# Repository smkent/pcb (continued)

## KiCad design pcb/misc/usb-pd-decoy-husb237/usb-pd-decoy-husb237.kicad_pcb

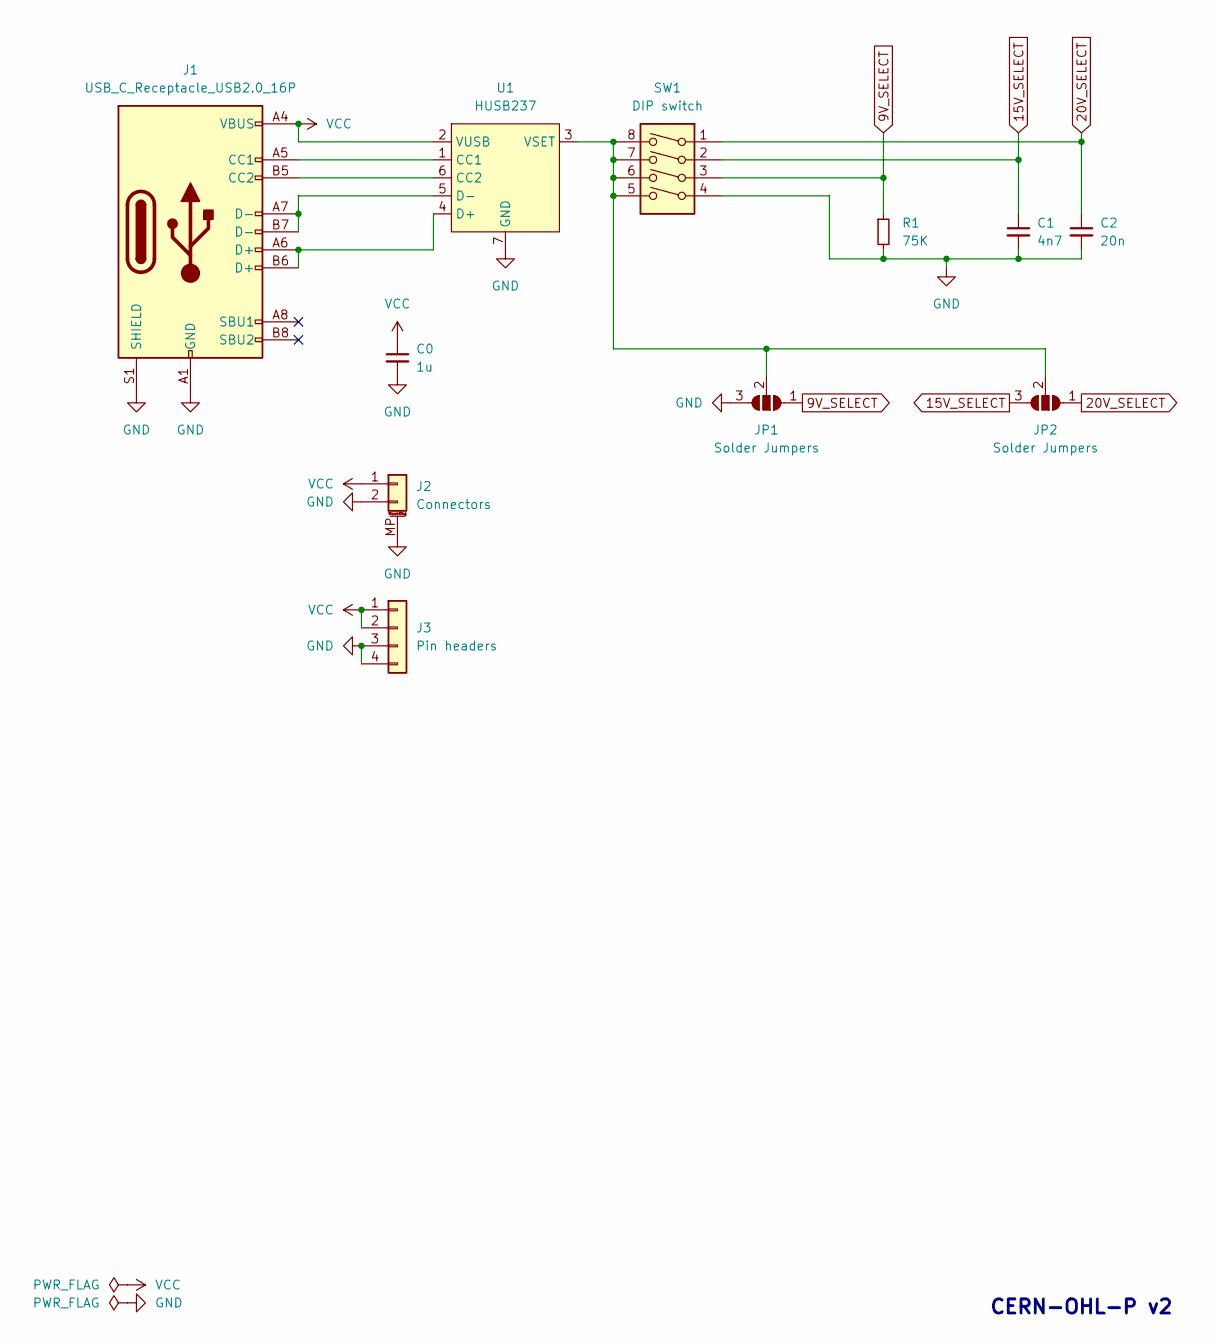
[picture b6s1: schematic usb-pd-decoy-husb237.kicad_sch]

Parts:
C0: 1u; C_0603_1608Metric_Pad1.08x0.95mm_HandSolder
C1: 4n7; C_0603_1608Metric_Pad1.08x0.95mm_HandSolder
C2: 20n; C_0603_1608Metric_Pad1.08x0.95mm_HandSolder
J1: USB_C_Receptacle_USB2.0_16P; USB_C_Receptacle_GCT_USB4105-xx-A_16P_TopMnt_Horizontal
J2: Connectors; Conn_Combo_TerminalBlock_JST-1x02-XH_PH-pad2gnd
J3: Pin headers; PinHeader_1x04_P2.54mm_Vertical_simple_pad3,4gnd
JP1, JP2: Solder Jumpers; SolderJumper-3_P1.0mm_Open_RoundedPad_simple
R1: 75K; R_0603_1608Metric_Pad0.98x0.95mm_HandSolder
SW1: DIP switch; SW_DIP_SPSTx04_Slide_P1.27mm
U1: HUSB237; DFN-6-1EP_2x2mm_P0.65mm_EP1x1.6mm; LCSC Part C7471904

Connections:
9V_SELECT: JP1.1 (A), R1.1, SW1.3
15V_SELECT: C1.1, JP2.3 (B), SW1.2
20V_SELECT: C2.1, JP2.1 (A), SW1.1
GND: C0.2, C1.2, C2.2, J1.A1 (GND), J1.A12 (GND), J1.B1 (GND), J1.B12 (GND), J1.S1 (SHIELD), J2.2, J2.MP (MountPin), J3.3, J3.4, JP1.3 (B), R1.2, SW1.4, U1.7 (GND)
unnamed: J1.A5 (CC1), U1.1 (CC1)
unnamed: J1.B5 (CC2), U1.6 (CC2)
unnamed: JP1.2 (C), JP2.2 (C), SW1.5, SW1.6, SW1.7, SW1.8, U1.3 (VSET)
unnamed: J1.A6 (D+), J1.B6 (D+), U1.4 (D+)
unnamed: J1.A7 (D-), J1.B7 (D-), U1.5 (D-)
VCC: C0.1, J1.A4 (VBUS), J1.A9 (VBUS), J1.B4 (VBUS), J1.B9 (VBUS), J2.1, J3.1, J3.2, U1.2 (VUSB)

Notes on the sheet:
CERN-OHL-P v2

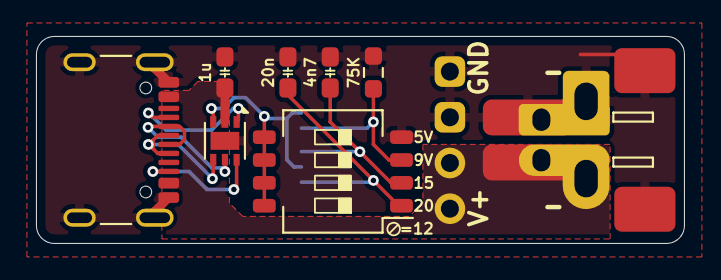
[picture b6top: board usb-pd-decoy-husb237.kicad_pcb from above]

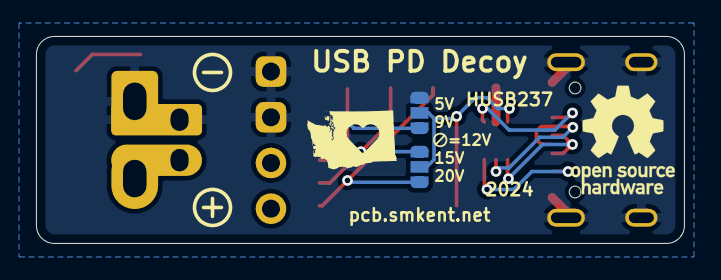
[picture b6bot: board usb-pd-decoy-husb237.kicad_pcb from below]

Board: 2 copper layers, 36.0 x 11.5 mm, 11 parts (3 on the bottom side), 10 nets.

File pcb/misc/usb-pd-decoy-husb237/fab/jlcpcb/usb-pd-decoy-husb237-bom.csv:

Comment,Designator,Footprint,LCSC
HUSB237,U1,Package_DFN_QFN:DFN-6-1EP_2x2mm_P0.65mm_EP1x1.6mm,C7471904
1u,C0,custom:C_0603_1608Metric_Pad1.08x0.95mm_HandSolder,
75K,R1,custom:R_0603_1608Metric_Pad0.98x0.95mm_HandSolder_simple,
20n,C2,custom:C_0603_1608Metric_Pad1.08x0.95mm_HandSolder,
DIP switch,SW1,custom:SW_DIP_SPSTx04_Slide_P1.27mm,
USB_C_Receptacle_USB2.0_16P,J1,connectors:USB-C-Receptacle-16P-TopMount-Horizontal,
4n7,C1,custom:C_0603_1608Metric_Pad1.08x0.95mm_HandSolder,
Pin headers,J3,"custom:PinHeader_1x04_P2.54mm_Vertical_simple_pad3,4gnd",
Connectors,J2,custom:Conn_Combo_TerminalBlock_JST-1x02-XH_PH-pad2gnd,

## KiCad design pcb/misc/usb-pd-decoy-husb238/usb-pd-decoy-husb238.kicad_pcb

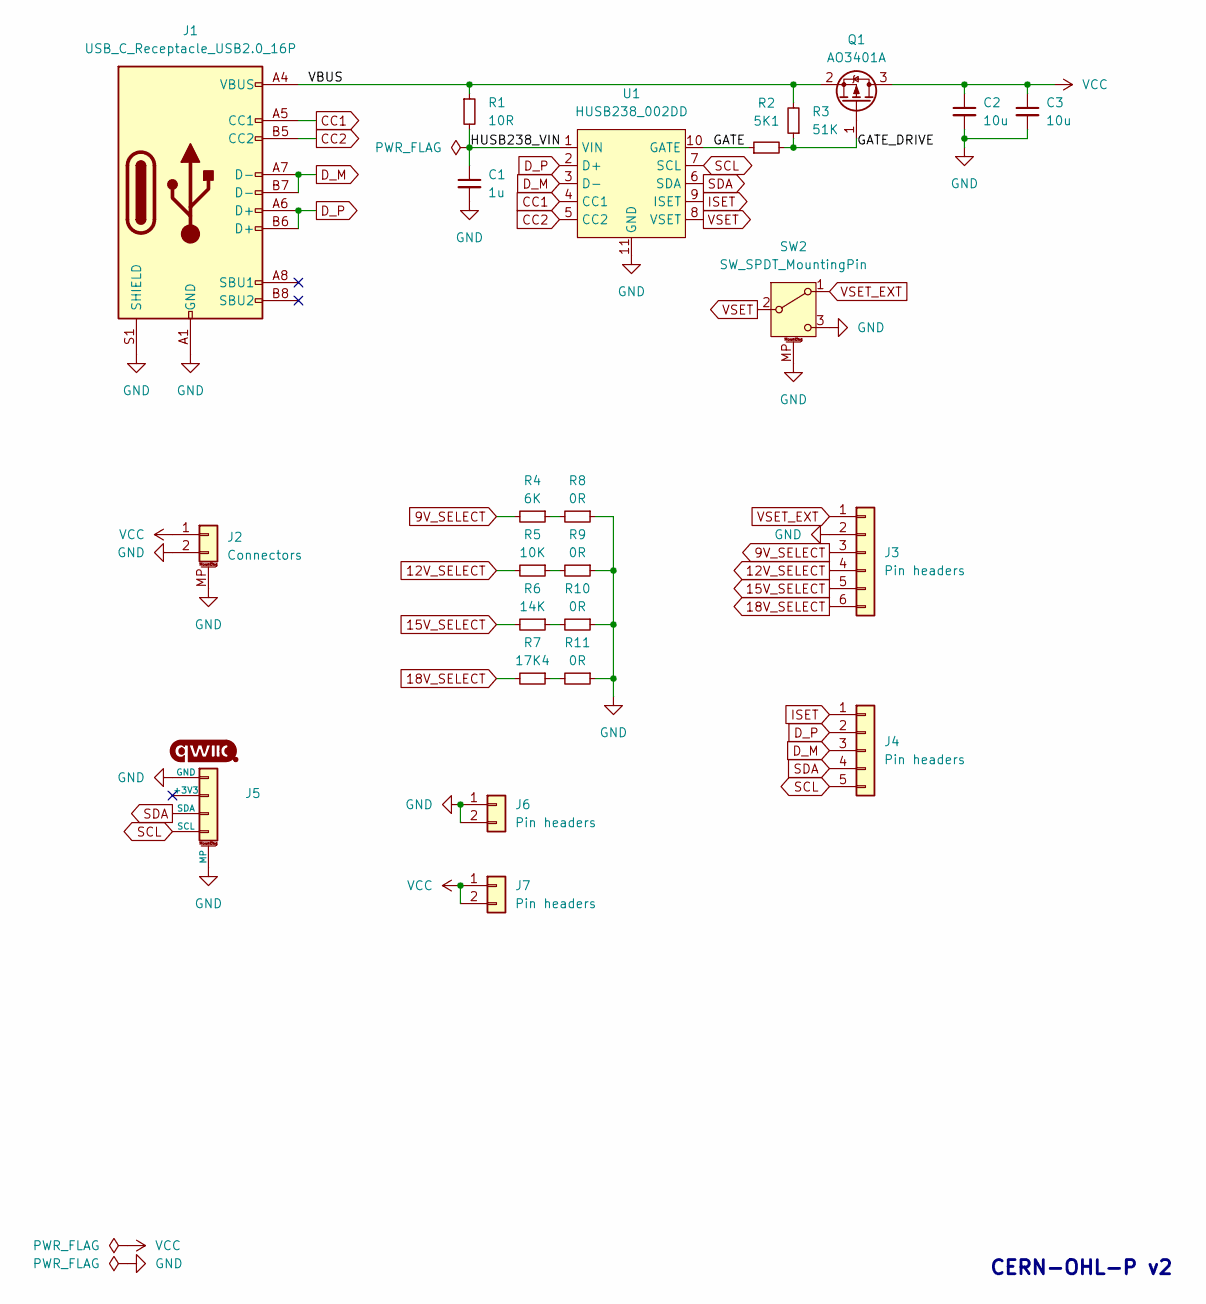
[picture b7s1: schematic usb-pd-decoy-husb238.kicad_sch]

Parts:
C1: 1u; C_0603_1608Metric
C2, C3: 10u; C_0603_1608Metric
J1: USB_C_Receptacle_USB2.0_16P; USB_C_Receptacle_GCT_USB4105-xx-A_16P_TopMnt_Horizontal
J2: Connectors; Conn_Combo_TerminalBlock_JST-1x02-XH_PH-pad2gnd
J3: Pin headers; PinHeader_1x06_P2.54mm_Vertical_simple
J4: Pin headers; PinHeader_1x05_P2.54mm_Vertical_simple
J5: Qwiic; Qwiic-SMD-horizontal-logo-bottom-pinout
J6, J7: Pin headers; PinHeader_1x02_P2.54mm_Vertical_simple
Q1: AO3401A; SOT-23
R1: 10R; R_0603_1608Metric
R2: 5K1; R_0603_1608Metric
R3: 51K; R_0603_1608Metric
R4: 6K; R_0603_1608Metric
R5: 10K; R_0603_1608Metric
R6: 14K; R_0603_1608Metric
R7: 17K4; R_0603_1608Metric
R8, R9, R10, R11: 0R; R_0603_1608Metric
SW2: SW_SPDT_MountingPin; SW_SPDT_PCM12
U1: HUSB238_002DD; WDFN-10-1EP_3x3mm_P0.5mm_EP1.8x2.5mm; LCSC Part C7471904

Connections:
9V_SELECT: J3.3, R4.2
12V_SELECT: J3.4, R5.2
15V_SELECT: J3.5, R6.2
18V_SELECT: J3.6, R7.2
/GATE: R2.1, U1.10 (GATE)
/GATE_DRIVE: Q1.1 (G), R2.2, R3.1
/HUSB238_VIN: C1.1, R1.2, U1.1 (VIN)
/VBUS: J1.A4 (VBUS), J1.A9 (VBUS), J1.B4 (VBUS), J1.B9 (VBUS), Q1.2 (S), R1.1, R3.2
CC1: J1.A5 (CC1), U1.4 (CC1)
CC2: J1.B5 (CC2), U1.5 (CC2)
D_M: J1.A7 (D-), J1.B7 (D-), J4.3, U1.3 (D-)
D_P: J1.A6 (D+), J1.B6 (D+), J4.2, U1.2 (D+)
GND: C1.2, C2.2, C3.2, J1.A1 (GND), J1.A12 (GND), J1.B1 (GND), J1.B12 (GND), J1.S1 (SHIELD), J2.2, J2.MP (MountPin), J3.2, J5.1 (GND), J5.MP, J6.1, J6.2, R8.1, R9.1, R10.1, R11.1, SW2.3 (C), SW2.MP (MountPin), U1.11 (GND)
ISET: J4.1, U1.9 (ISET)
unnamed: R4.1, R8.2
unnamed: R5.1, R9.2
unnamed: R6.1, R10.2
unnamed: R7.1, R11.2
SCL: J4.5, J5.4 (SCL), U1.7 (SCL)
SDA: J4.4, J5.3 (SDA), U1.6 (SDA)
VCC: C2.1, C3.1, J2.1, J7.1, J7.2, Q1.3 (D)
VSET: SW2.2 (B), U1.8 (VSET)
VSET_EXT: J3.1, SW2.1 (A)

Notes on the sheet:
CERN-OHL-P v2

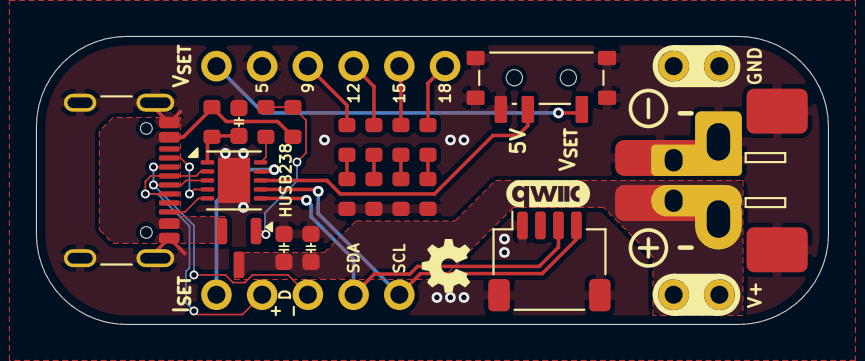
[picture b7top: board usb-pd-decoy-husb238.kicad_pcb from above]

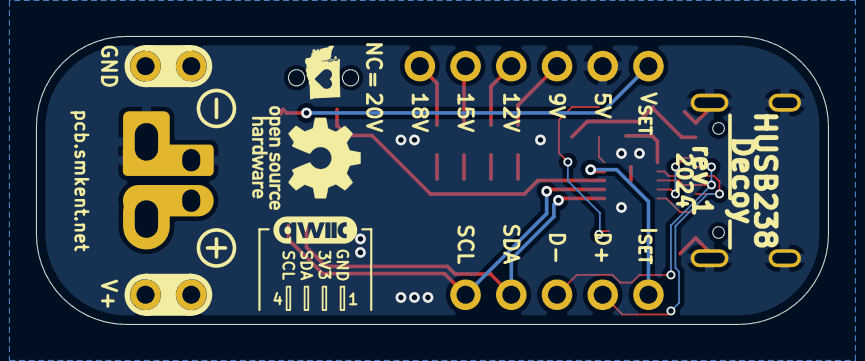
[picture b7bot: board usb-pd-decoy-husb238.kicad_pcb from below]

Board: 2 copper layers, 44.0 x 16.0 mm, 24 parts (4 on the bottom side), 23 nets.
